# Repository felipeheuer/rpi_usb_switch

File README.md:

# Raspberry Pi controlled USB switch

This is a simple project that allows you to enable/disable power lines from 5 USB ports individually over 5 GPIO's from a Raspberry Pi.

Was initially made to re-use an old dead USB hub that was laying down on my drawers an recycle it into a nice hub for powering up my LED gadgets.
The Mosfet circuitry layout is based on a generic circuit found on Amazon from different brands, but might have [this guy](https://michiel.vanderwulp.be/domotica/Modules/MosFetPwmDriveModule/) as a father.

**Data lines are disabled, this is only used for devices that have USB port as power source.**

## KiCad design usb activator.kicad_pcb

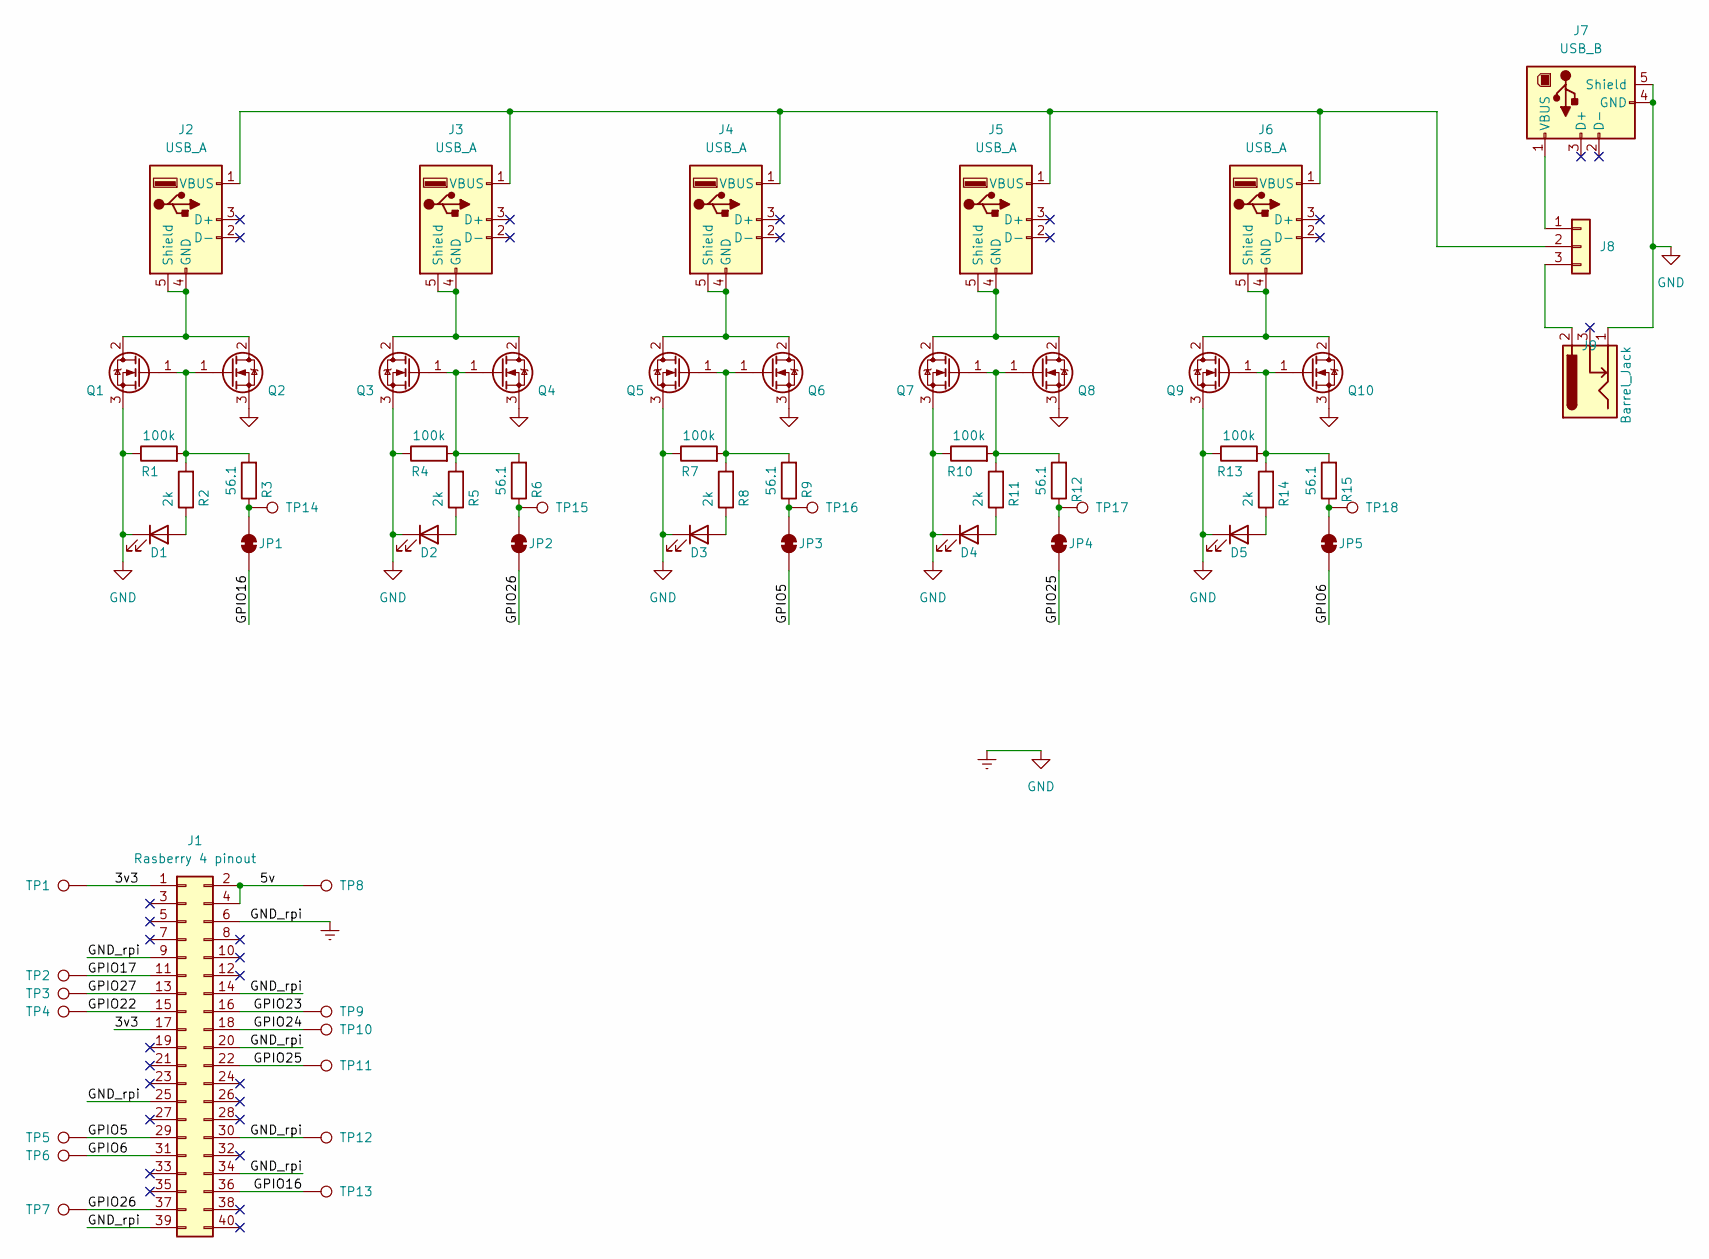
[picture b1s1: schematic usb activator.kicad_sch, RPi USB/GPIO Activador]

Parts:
D1, D2, D3, D4, D5: LED; LED_0805_2012Metric_Pad1.15x1.40mm_HandSolder
J1: Rasberry 4 pinout; Header_Board_Edge_2x20
J2, J3, J4, J5, J6: USB_A; USB_A_Generic_Vertical
J7: USB_B; USB_B_Lumberg_2411_02_Horizontal
J8: Conn_02x03_Counter_Clockwise; PinHeader_1x03_P2.54mm_Vertical
J9: Barrel_Jack; PinHeader_1x03_P2.54mm_Vertical
JP1, JP2, JP3, JP4, JP5: SolderJumper_2_Bridged; SolderJumper-2_P1.3mm_Bridged_RoundedPad1.0x1.5mm
Q1, Q2, Q3, Q4, Q5, Q6, Q7, Q8, Q9, Q10: IPD50R3K0CE; TO-252-2
R1, R4, R7, R10, R13: 100k; R_0805_2012Metric_Pad1.20x1.40mm_HandSolder
R2, R5, R8, R11, R14: 2k; R_0805_2012Metric_Pad1.20x1.40mm_HandSolder
R3, R6, R9, R12, R15: 56.1; R_0805_2012Metric_Pad1.20x1.40mm_HandSolder
TP1, TP2, TP3, TP4, TP5, TP6, TP7, TP8, TP9, TP10, TP11, TP12, TP13, TP14, TP15, TP16, TP17, TP18: TestPoint; TestPoint_Pad_D1.0mm

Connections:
/3v3: J1.1, J1.17, TP1.1
/5v: J1.2, J1.4, TP8.1
/GPIO5: J1.29, JP3.1 (A), TP5.1
/GPIO6: J1.31, JP5.1 (A), TP6.1
/GPIO16: J1.36, JP1.1 (A), TP13.1
/GPIO17: J1.11, TP2.1
/GPIO22: J1.15, TP4.1
/GPIO23: J1.16, TP9.1
/GPIO24: J1.18, TP10.1
/GPIO25: J1.22, JP4.1 (A), TP11.1
/GPIO26: J1.37, JP2.1 (A), TP7.1
/GPIO27: J1.13, TP3.1
GND: D1.1 (K), D2.1 (K), D3.1 (K), D4.1 (K), D5.1 (K), J1.6, J1.9, J1.14, J1.20, J1.25, J1.30, J1.34, J1.39, J7.4 (GND), J7.5 (Shield), J9.1, Q1.3 (S), Q2.3 (S), Q3.3 (S), Q4.3 (S), Q5.3 (S), Q6.3 (S), Q7.3 (S), Q8.3 (S), Q9.3 (S), Q10.3 (S), R1.1, R4.1, R7.1, R10.1, R13.1, TP12.1
unnamed: D1.2 (A), R2.1
unnamed: D2.2 (A), R5.1
unnamed: D3.2 (A), R8.1
unnamed: D4.2 (A), R11.1
unnamed: D5.2 (A), R14.1
unnamed: J2.1 (VBUS), J3.1 (VBUS), J4.1 (VBUS), J5.1 (VBUS), J6.1 (VBUS), J8.2
unnamed: J2.4 (GND), J2.5 (Shield), Q1.2 (D), Q2.2 (D)
unnamed: J3.4 (GND), J3.5 (Shield), Q3.2 (D), Q4.2 (D)
unnamed: J4.4 (GND), J4.5 (Shield), Q5.2 (D), Q6.2 (D)
unnamed: J5.4 (GND), J5.5 (Shield), Q7.2 (D), Q8.2 (D)
unnamed: J6.4 (GND), J6.5 (Shield), Q9.2 (D), Q10.2 (D)
unnamed: J7.1 (VBUS), J8.1
unnamed: J8.3, J9.2
unnamed: JP1.2 (B), R3.1, TP14.1
unnamed: JP2.2 (B), R6.1, TP15.1
unnamed: JP3.2 (B), R9.1, TP16.1
unnamed: JP4.2 (B), R12.1, TP17.1
unnamed: JP5.2 (B), R15.1, TP18.1
unnamed: Q1.1 (G), Q2.1 (G), R1.2, R2.2, R3.2
unnamed: Q3.1 (G), Q4.1 (G), R4.2, R5.2, R6.2
unnamed: Q5.1 (G), Q6.1 (G), R7.2, R8.2, R9.2
unnamed: Q7.1 (G), Q8.1 (G), R10.2, R11.2, R12.2
unnamed: Q9.1 (G), Q10.1 (G), R13.2, R14.2, R15.2

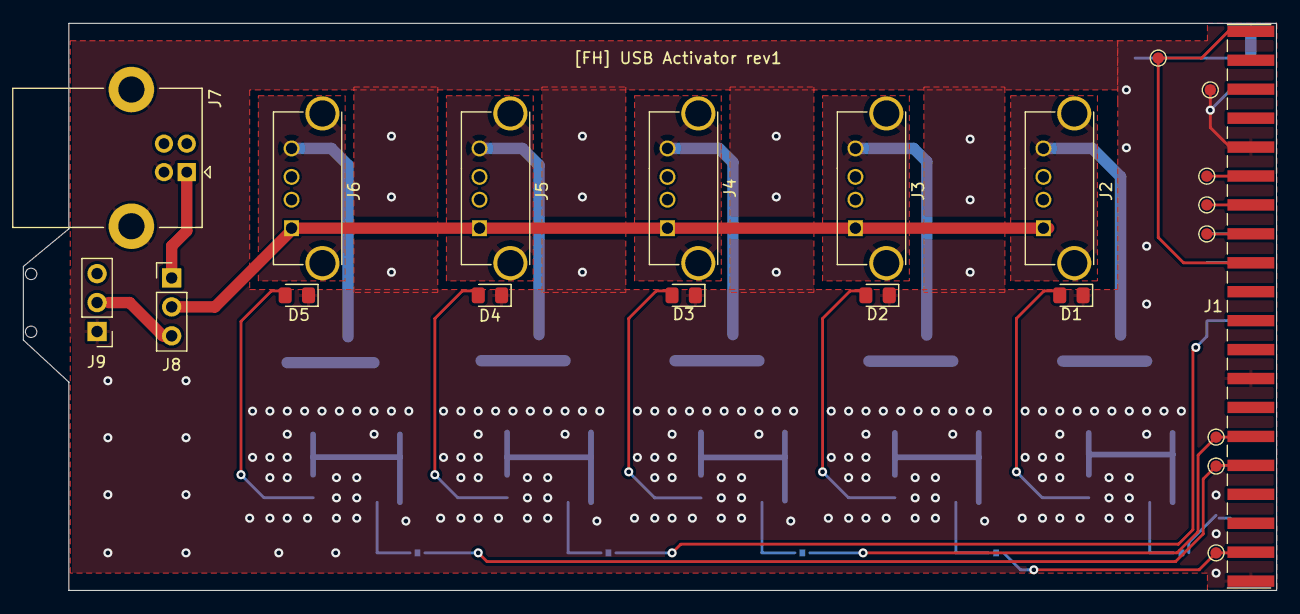
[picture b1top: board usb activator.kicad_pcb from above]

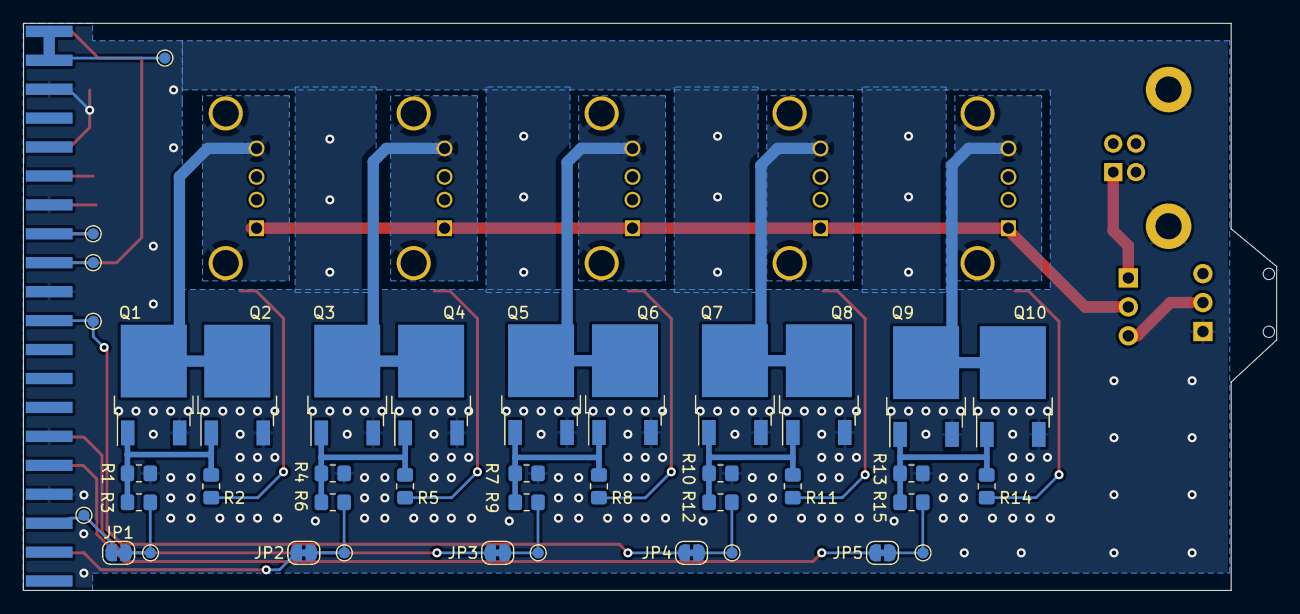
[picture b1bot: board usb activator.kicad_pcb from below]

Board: 2 copper layers, 110.0 x 49.8 mm, 62 parts (40 on the bottom side), 36 nets.

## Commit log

2023-01-21 rev 1
    First commit
2023-01-21 fix: adds 3d files for custom lib
2023-01-21 chore: adds social image and gitignore
